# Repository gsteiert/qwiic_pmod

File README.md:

# qwiic_pmod

## Theory of operation

This board connects a MachXO2 between a Qwiic connector and several PMOD connectors.  There is also a small joystic and LEDs for user I/O. There is also a footprint for an oscillator and a button on the program pin.

### I2C

The MachXO2 has hard I2C and SPI blocks that can be used to program the device and are also available to be used in the application.  You shuold note that there are two sets of I2C pins connected to the Qwiic connector.  One goes to the hard I2C block for programming the device, and the other is intended for the user's application.  The hard I2C block works well for programming, but it has some limitations that make it difficult to use in an application.  I would only ever suggest using the hard I2C controller as a master in a user application.  Using the hard controller as an I2C slave should be avoided at all costs. 

Connecting two ports to the connector also simplifies programming.  Choose two different I2C addresses so you can update the code without switching to a programming mode.  The device will always be listening for updates on one address while your application communicate with the other address.

### SPI

The PMOD connector opposite the Qwiic connector is wired up to the MachXO2 SPI programming lines as a peripheral PMOD if you wish to load the part through SPI

### JTAG

The JTAG pins are brought to a tag-connect footprint if needed for recovery.

### Recovery

User applications can disable or interfere with the I2C programming port.  If the image loaded into the device is preventing programming, you should hold down the program button and erase the device while the button remains pressed.

### Feature Row

The default blank state of the feature row enables programming through I2C and SPI, but it can dissable these ports.  In fact, the default settings for these bits in Diamond will dissable them unless you go in and change it from the default in the global settings.  When programming the device through I2C or SPI I suggest to avoid programming the feature row unless absolutely necessary.  My example code for loading the device from CircuitPython or Arduino ignore the feature row in the Jedec file for this reason.  The feature row should not be updated with most program updates, only when necessary.

### Programming Examples

These libraries suppoprt both I2C or SPI

* CircuitPython:  [machXOprog](https://github.com/gsteiert/machXOprog)
* Arduino:  [MachXO_Library](https://github.com/gsteiert/MachXO_Library)

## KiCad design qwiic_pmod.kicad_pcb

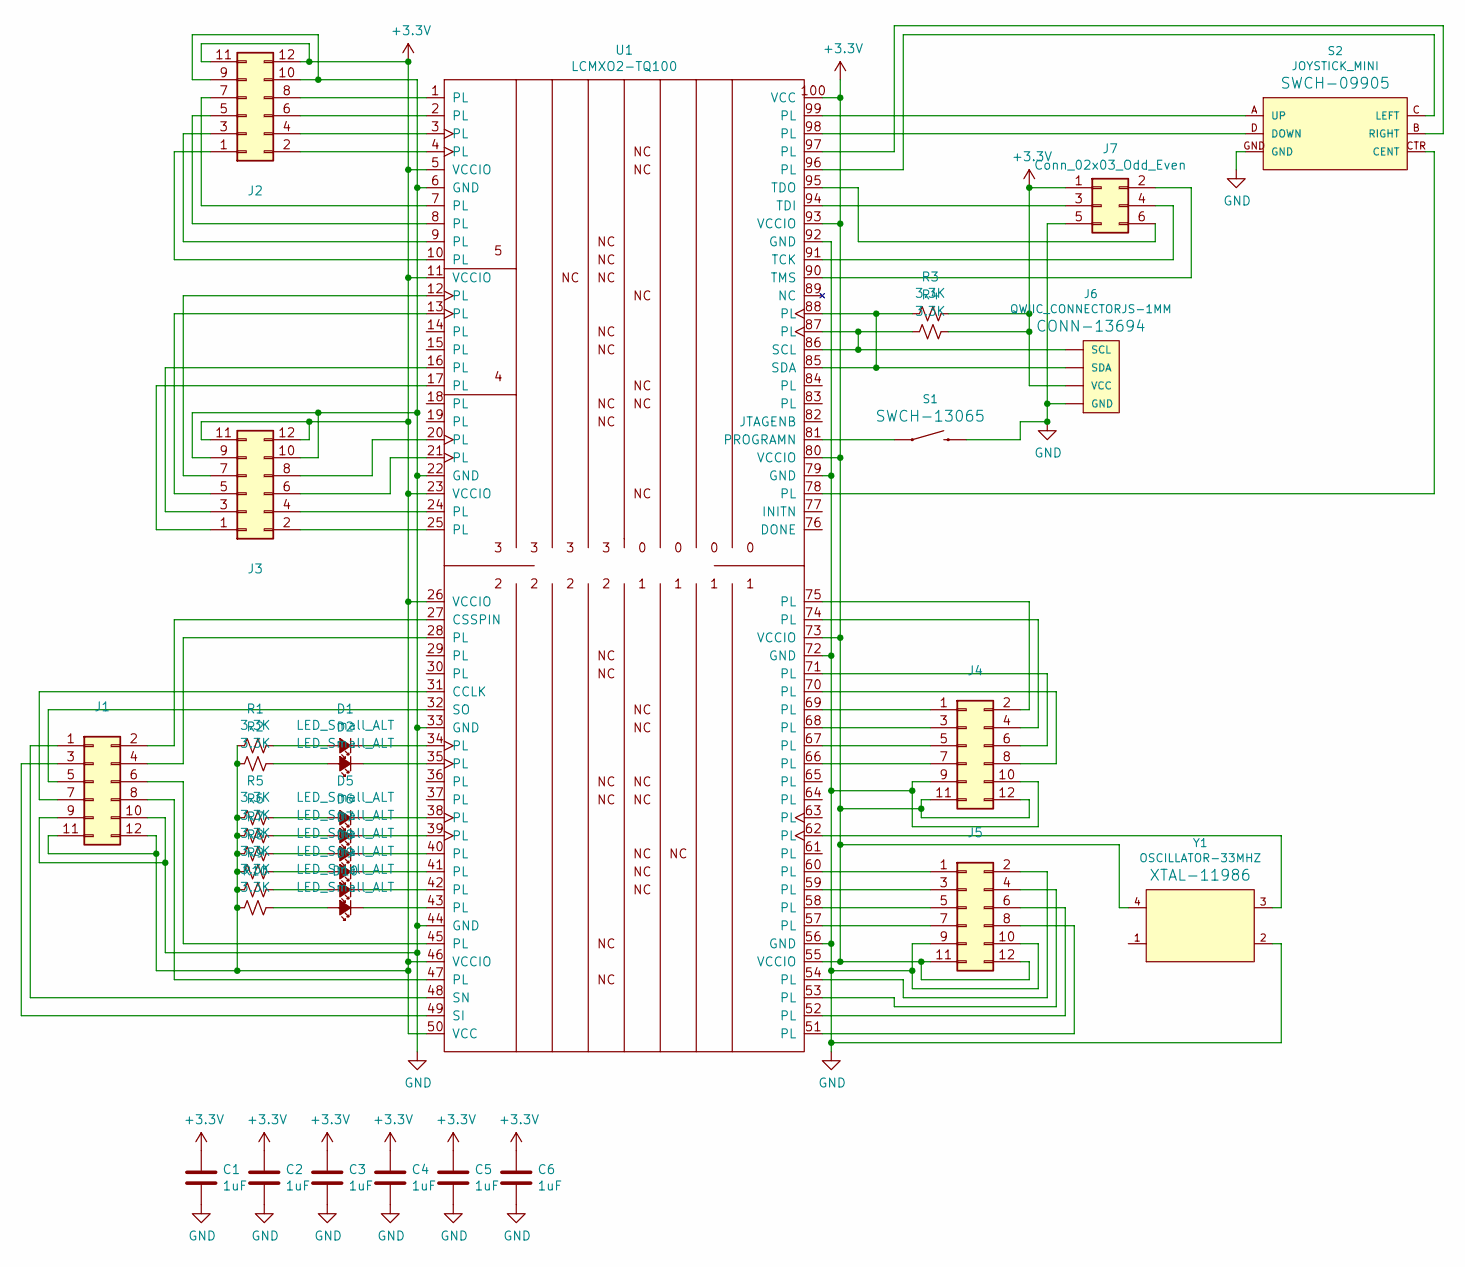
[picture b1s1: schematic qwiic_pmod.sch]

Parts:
C1, C2, C3, C4, C5, C6: 1uF; C_0402_1005Metric
D1, D2, D5, D6, D7, D8, D9, D10: LED_Small_ALT; LED_0402_1005Metric
J1, J2, J3, J4, J5: Conn_02x06_Top_Bottom; Samtec_HLE-106-02-xxx-DV-BE_2x06_P2.54mm_Horizontal
J6: QWIIC_CONNECTORJS-1MM; 1X04_1MM_RA
J7: Conn_02x03_Odd_Even; Tag-Connect_TC2030-IDC-NL_2x03_P1.27mm_Vertical
R1, R2, R3, R4, R5, R6, R7, R8, R9, R10: 3.3K; R_0402_1005Metric
S1: MOMENTARY-SWITCH-SPST-SMD-4.6X2.8MM; TACTILE_SWITCH_SMD_4.6X2.8MM
S2: JOYSTICK_MINI
U1: LCMXO2-TQ100; LQFP-100_14x14mm_P0.5mm
Y1: OSCILLATOR-33MHZ; OSCILLATOR-SMD-5X3.2

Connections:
+3V3: C1.1, C2.1, C3.1, C4.1, C5.1, C6.1, J1.11, J1.12, J2.11, J2.12, J3.11, J3.12, J4.11, J4.12, J5.11, J5.12, J6.2 (VCC), J7.1, R1.2, R2.2, R3.1, R4.1, R5.2, R6.2, R7.2, R8.2, R9.2, R10.2, U1.5 (VCCIO), U1.11 (VCCIO), U1.23 (VCCIO), U1.26 (VCCIO), U1.46 (VCCIO), U1.50 (VCC), U1.55 (VCCIO), U1.73 (VCCIO), U1.80 (VCCIO), U1.93 (VCCIO), U1.100 (VCC), Y1.4 (VCC); also elsewhere on the board
GND: C1.2, C2.2, C3.2, C4.2, C5.2, C6.2, J1.9, J1.10, J2.9, J2.10, J3.9, J3.10, J4.9, J4.10, J5.9, J5.10, J6.1 (GND), J7.5, S1.3 (2), S1.4 (2), S2.GND, U1.6 (GND), U1.22 (GND), U1.33 (GND), U1.44 (GND), U1.56 (GND), U1.72 (GND), U1.79 (GND), U1.92 (GND), Y1.2 (GND); also elsewhere on the board
unnamed: D1.1 (K), U1.34 (PL)
unnamed: D1.2 (A), R1.1
unnamed: D2.1 (K), U1.35 (PL)
unnamed: D2.2 (A), R2.1
unnamed 6: U1.77 (INITN); also elsewhere on the board
unnamed 8: U1.76 (DONE); also elsewhere on the board
unnamed: D5.1 (K), U1.38 (PL)
unnamed: D5.2 (A), R5.1
unnamed: D6.1 (K), U1.39 (PL)
unnamed: D6.2 (A), R6.1
unnamed: D7.1 (K), U1.40 (PL)
unnamed: D7.2 (A), R7.1
unnamed: D8.1 (K), U1.41 (PL)
unnamed: D8.2 (A), R8.1
unnamed: D9.1 (K), U1.42 (PL)
unnamed: D9.2 (A), R9.1
unnamed: D10.1 (K), U1.43 (PL)
unnamed: D10.2 (A), R10.1
unnamed: J1.1, U1.48 (SN)
unnamed: J1.2, U1.27 (CSSPIN)
unnamed: J1.3, U1.49 (SI)
unnamed: J1.4, U1.28 (PL)
unnamed: J1.5, U1.32 (SO)
unnamed: J1.6, U1.45 (PL)
unnamed: J1.7, U1.31 (CCLK)
unnamed: J1.8, U1.47 (PL)
unnamed: J2.1, U1.10 (PL)
unnamed: J2.2, U1.4 (PL)
unnamed: J2.3, U1.9 (PL)
unnamed: J2.4, U1.3 (PL)
unnamed: J2.5, U1.8 (PL)
unnamed: J2.6, U1.2 (PL)
unnamed: J2.7, U1.7 (PL)
unnamed: J2.8, U1.1 (PL)
unnamed: J3.1, U1.17 (PL)
unnamed: J3.2, U1.25 (PL)
unnamed: J3.3, U1.16 (PL)
unnamed: J3.4, U1.24 (PL)
unnamed: J3.5, U1.13 (PL)
unnamed: J3.6, U1.21 (PL)
unnamed: J3.7, U1.12 (PL)
unnamed: J3.8, U1.20 (PL)
unnamed: J4.1, U1.69 (PL)
unnamed: J4.2, U1.75 (PL)
unnamed: J4.3, U1.68 (PL)
unnamed: J4.4, U1.74 (PL)
unnamed: J4.5, U1.67 (PL)
unnamed: J4.6, U1.71 (PL)
unnamed: J4.7, U1.66 (PL)
unnamed: J4.8, U1.70 (PL)
unnamed: J5.1, U1.60 (PL)
unnamed: J5.2, U1.54 (PL)
unnamed: J5.3, U1.59 (PL)
unnamed: J5.4, U1.53 (PL)
unnamed: J5.5, U1.58 (PL)
unnamed: J5.6, U1.52 (PL)
unnamed: J5.7, U1.57 (PL)
unnamed: J5.8, U1.51 (PL)
unnamed: J6.3 (SDA), R3.2, U1.85 (SDA), U1.88 (PL)
unnamed: J6.4 (SCL), R4.2, U1.86 (SCL), U1.87 (PL)
unnamed: J7.2, U1.90 (TMS)
unnamed: J7.3, U1.94 (TDI)
unnamed: J7.4, U1.91 (TCK)
unnamed: J7.6, U1.95 (TDO)
unnamed: S1.1, S1.2 (1), U1.81 (PROGRAMN)
unnamed: S2.A (UP), U1.99 (PL)
unnamed: S2.B (RIGHT), U1.97 (PL)
unnamed: S2.C (LEFT), U1.96 (PL)
unnamed: S2.CTR (CENT), U1.78 (PL)
unnamed: S2.D (DOWN), U1.98 (PL)
unnamed: U1.62 (PL), Y1.3 (OUT)

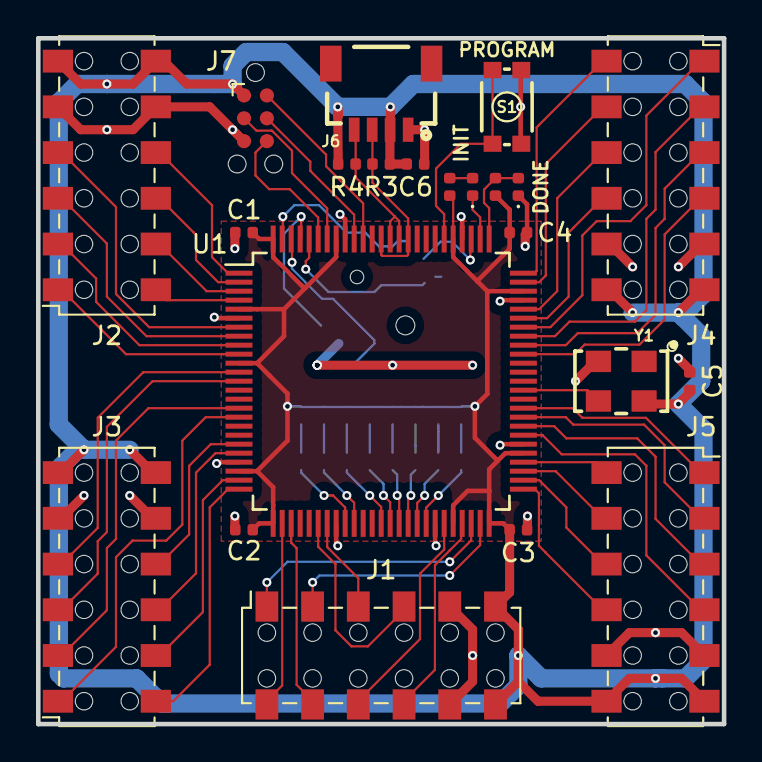
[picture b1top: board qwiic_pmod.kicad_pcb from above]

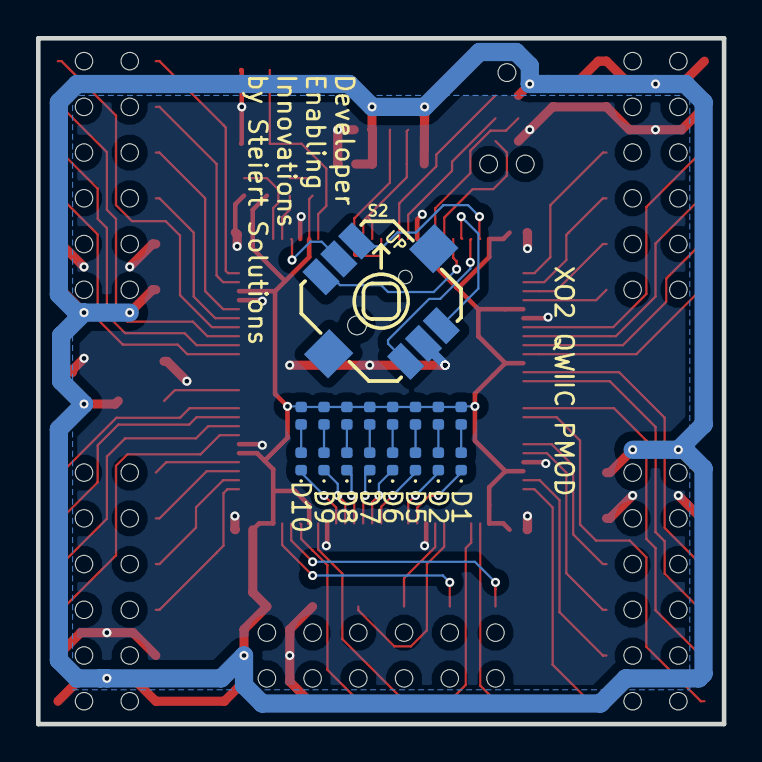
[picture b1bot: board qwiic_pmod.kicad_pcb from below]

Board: 2 copper layers, 38.1 x 38.1 mm, 39 parts (17 on the bottom side), 74 nets.

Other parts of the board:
D3, D4: LED_Small_ALT; LED_0402_1005Metric
R11, R12: 3.3K; R_0402_1005Metric

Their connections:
+3V3: R11.1, R12.1; also elsewhere on the board
GND: D4.1; also elsewhere on the board
unnamed 6: D3.1; also elsewhere on the board
unnamed: D3.2, R11.2
unnamed 8: D4.2, R12.2; also elsewhere on the board

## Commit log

2020-08-07 added pdf sch
2020-08-07 fixed typo
